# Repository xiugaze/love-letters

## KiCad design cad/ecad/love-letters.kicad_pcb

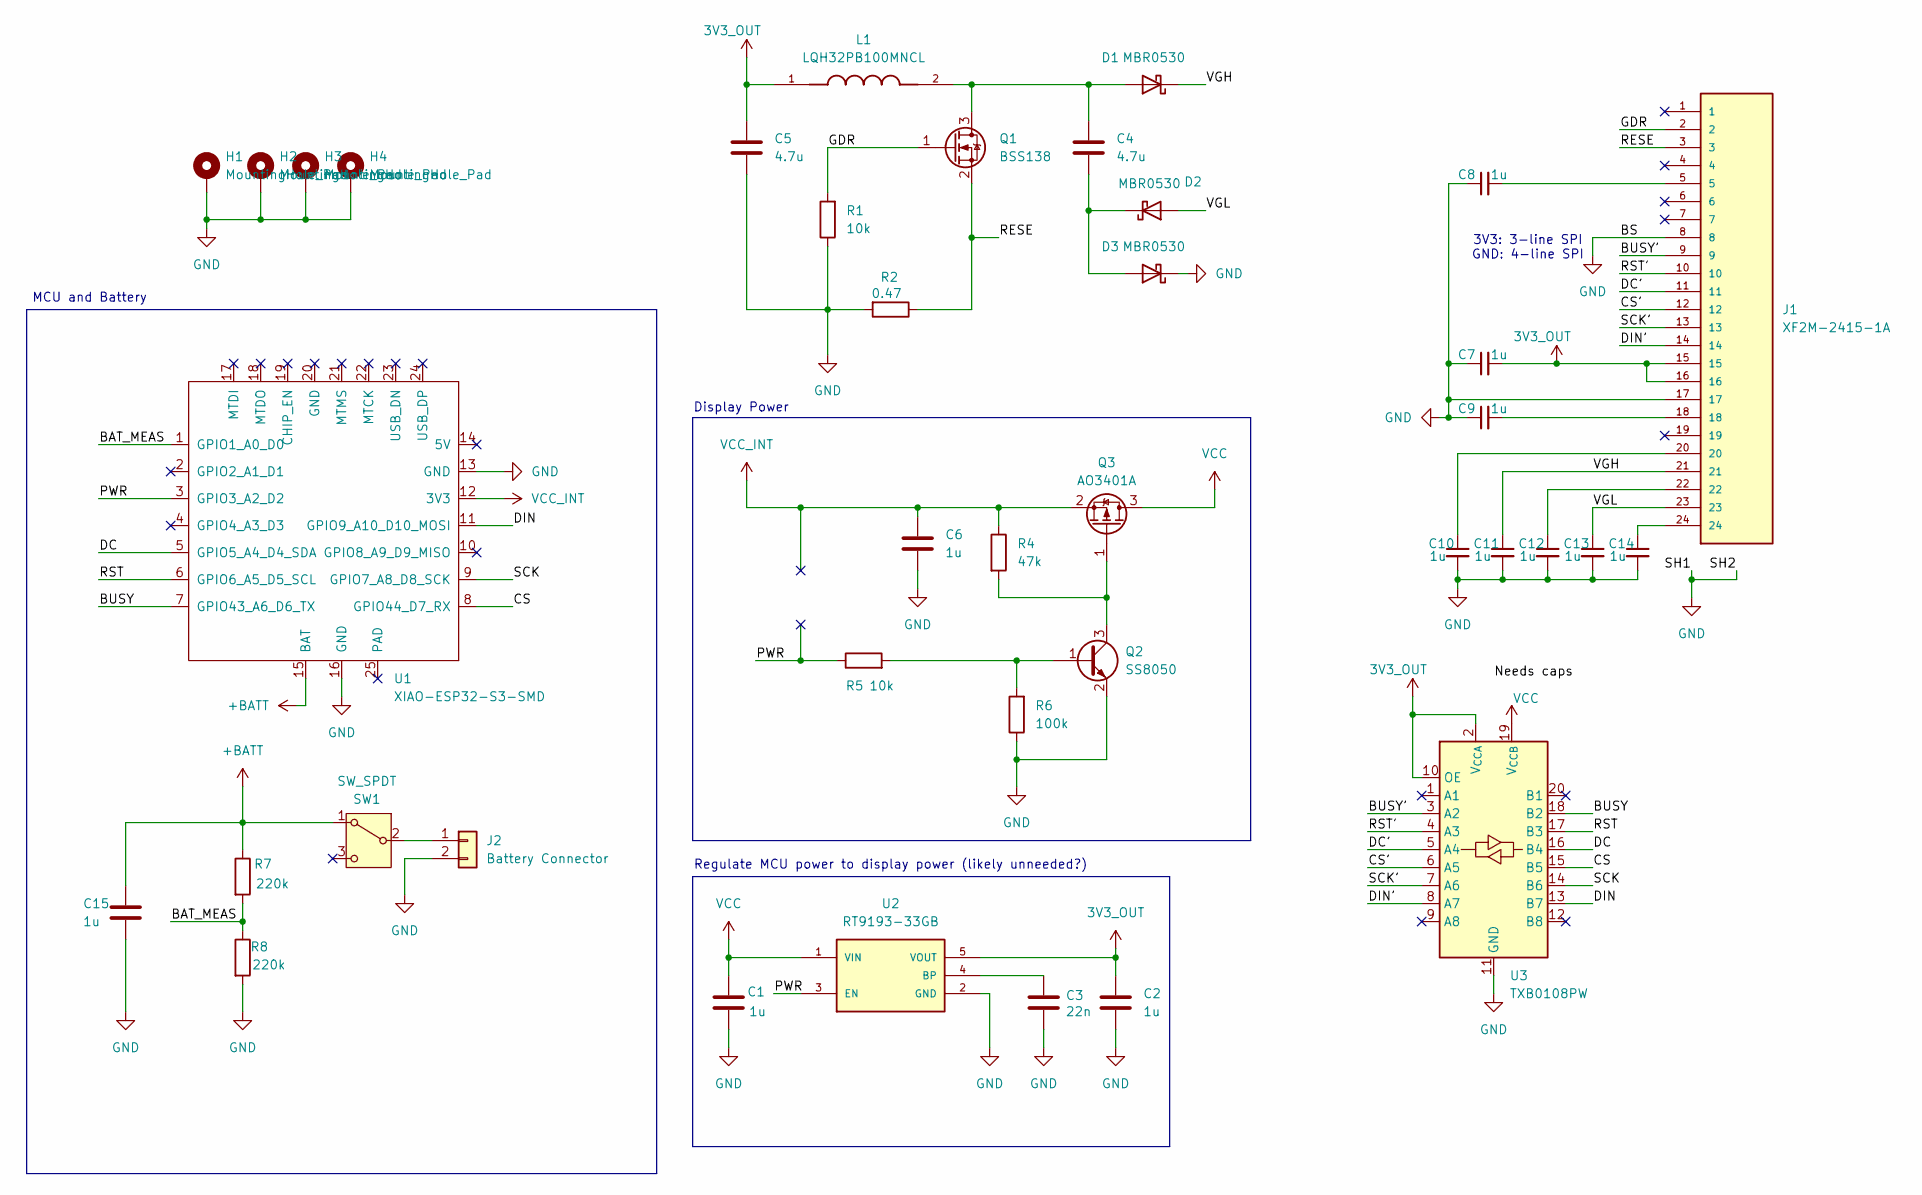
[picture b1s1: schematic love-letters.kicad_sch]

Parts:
C1, C2, C6, C7, C8, C9, C10, C11, C12, C13, C14, C15: 1u; C_0805_2012Metric
C3: 22n; C_0805_2012Metric
C4, C5: 4.7u; C_0805_2012Metric
D1, D2, D3: MBR0530; D_SOD-123
H1, H2, H3, H4: MountingHole_Pad; MountingHole_2.2mm_M2_Pad
J1: XF2M-2415-1A; OMRON_XF2M-2415-1A
J2: Battery Connector; JST_EH_S2B-EH_1x02_P2.50mm_Horizontal
L1: LQH32PB100MNCL; IND_LQH32PB100MNCL; PARTREV N/A; LCSC LQH32PB100MNCL C711133
Q1: BSS138; SOT-23; LCSC C52895
Q2: SS8050; SOT-23
Q3: AO3401A; SOT-23
R1, R5: 10k; R_0805_2012Metric
R2: 0.47; R_0805_2012Metric
R4: 47k; R_0805_2012Metric
R6: 100k; R_0805_2012Metric
R7, R8: 220k; R_0805_2012Metric
SW1: SW_SPDT; SW_SPDT_CK_JS102011SAQN
U1: XIAO-ESP32-S3-SMD; XIAO-ESP32S3-SMD; LCSC C9900154951
U2: RT9193-33GB; SOT94P279X129-5N
U3: TXB0108PW; TSSOP-20_4.4x6.5mm_P0.65mm

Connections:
3V3_OUT: C2.1, C5.1, C7.2, J1.15, J1.16, L1.1, U2.5 (VOUT), U3.2 (V_{CCA}), U3.10 (OE)
+BATT: C15.1, R7.1, SW1.1 (A), U1.15 (BAT)
/BAT_MEAS: R7.2, R8.1, U1.1 (GPIO1_A0_D0)
/BUSY: U1.7 (GPIO43_A6_D6_TX), U3.18 (B2)
/BUSY': J1.9, U3.3 (A2)
/CS: U1.8 (GPIO44_D7_RX), U3.15 (B5)
/CS': J1.12, U3.6 (A5)
/DC: U1.5 (GPIO5_A4_D4_SDA), U3.16 (B4)
/DC': J1.11, U3.5 (A4)
/DIN: U1.11 (GPIO9_A10_D10_MOSI), U3.13 (B7)
/DIN': J1.14, U3.8 (A7)
/GDR: J1.2, Q1.1 (G), R1.2
/PWR: R5.1, U1.3 (GPIO3_A2_D2), U2.3 (EN)
/RESE: J1.3, Q1.2 (S), R2.1
/RST: U1.6 (GPIO6_A5_D5_SCL), U3.17 (B3)
/RST': J1.10, U3.4 (A3)
/SCK: U1.9 (GPIO7_A8_D8_SCK), U3.14 (B6)
/SCK': J1.13, U3.7 (A6)
/VGH: C11.1, D1.1 (K), J1.21
/VGL: C13.1, D2.2 (A), J1.23
GND: C1.2, C2.2, C3.2, C5.2, C6.2, C7.1, C8.1, C9.1, C10.2, C11.2, C12.2, C13.2, C14.2, C15.2, D3.1 (K), H1.1, H2.1, H3.1, H4.1, J1.8, J1.17, J1.P1, J2.2, Q2.2 (E), R1.1, R2.2, R6.1, R8.2, U1.13 (GND), U1.16 (GND), U2.2 (GND), U3.11 (GND)
unnamed: C8.2, J1.5
unnamed: C9.2, J1.18
unnamed: C10.1, J1.20
unnamed: C12.1, J1.22
unnamed: C14.1, J1.24
unnamed: C4.1, D1.2 (A), L1.2, Q1.3 (D)
unnamed: C4.2, D2.1 (K), D3.2 (A)
unnamed: J2.1, SW1.2 (B)
unnamed: Q2.1 (B), R5.2, R6.2
unnamed: Q2.3 (C), Q3.1 (G), R4.2
unnamed: C3.1, U2.4 (BP)
VCC: C1.1, Q3.3 (D), U2.1 (VIN), U3.19 (V_{CCB})
VCC_INT: C6.1, Q3.2 (S), R4.1, U1.12 (3V3)

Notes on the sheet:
Display Power
Regulate MCU power to display power (likely unneeded?)
MCU and Battery
3V3: 3-line SPI GND: 4-line SPI

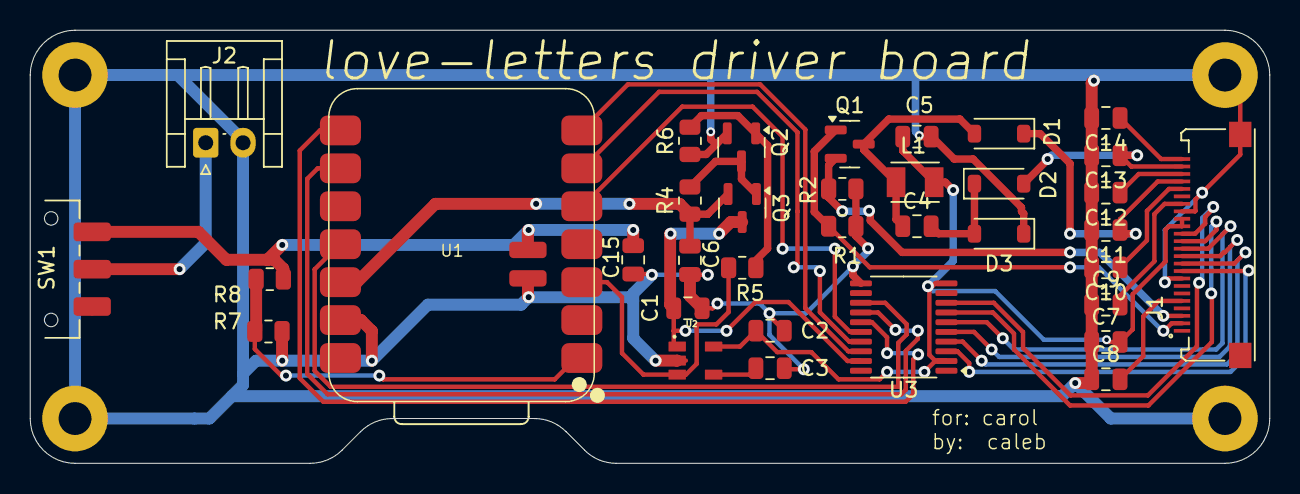
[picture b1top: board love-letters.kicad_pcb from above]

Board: 2 copper layers, 83.0 x 29.0 mm, 39 parts (0 on the bottom side), 34 nets.

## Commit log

2024-12-16 initial
2024-12-30 change: resolution -> 800x480 (waveshare display)
2024-12-30 fixed to work with pen
2024-12-30 feat: save svg, endpoint /get-svg serves
2025-01-02 integrate for flake config
2025-01-02 bump flake
2025-01-02 add error message
2025-01-02 fix: save path on javascript side
2025-01-02 add status message for error
2025-01-03 esp32-s3 pio project with svg retreival
2025-01-06 refactor for bmp data
2025-01-06 refactor to bitmapped binary data, justfile
2025-01-06 add bmp checks
2025-01-06 working esp32-s3 code
2025-01-06 remove waveshare-epd library
2025-01-17 working PIO project for XIAO-S3
2025-02-16 ecad: pcb rev 1 done
2025-04-02 Ordered Revision: Digikey and JLCPCB
